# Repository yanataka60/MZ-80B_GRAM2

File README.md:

# MZ-80B GRAM2ボード

　MZ-80B OWNER'S MANUAL p67「図4-21 グラフィックメモリ2 MZ-8BK(オプション)」回路図から基板を起こしました。

　本体への装着方法は純正品と同じです。

## 回路図
　KiCadフォルダ内のMZ-80B_GRAM2.pdf参照

[回路図](https://github.com/yanataka60/MZ-80B_GRAM2/blob/main/Kicad/MZ-80B_GRAM2.pdf)

## 部品表
|番号|品名|数量|備考|
| ------------ | ------------ | ------------ | ------------ |
|C1|電解コンデンサ 16V100uF|1||
|C2-C12, C14, C16-C18|積層セラミックコンデンサ 0.1uF|15||
|C13|コンデンサ 470pF|1||
|C15|コンデンサ 220pF|1||
|J2,J3,J4,J5|使用しません|||
|J6|2x5ピンヘッダ|1|秋月電子通商 PH-2x40SG等|
|R1,R2|カーボン抵抗 1k|2||
|R3|カーボン抵抗 47Ω|1||
|R4|カーボン抵抗 100Ω|1||
|U1-U3,U9|74LS157|4|若松通商等|
|U4|74LS245|1|若松通商等|
|U5,U6,U10|74LS93|3|若松通商等|
|U7|74LS165|1|若松通商等|
|U11|74LS107|1|若松通商等|
|U13|74LS00|1|若松通商等|
|U14|74LS04|1|若松通商等|
|U15,U18|74LS32|2|若松通商等|
|U19|8kx8 SRAM 6264|1|若松通商等|
||2x5フラットケーブル|1|4番スロットなら20cm程度、1番スロットなら30cm程度|

## ボードの完成写真

## 取付方法
拡張I/Oユニットの1番スロット又は4番スロットにGRAM2ボードを挿し込みます。

GRAM1ボードのJ3とGRAM2ボードのJ6を2x5Pinケーブルで接続します。

## 追記
2025.10.10 回路図のpdfファイルを追加した。

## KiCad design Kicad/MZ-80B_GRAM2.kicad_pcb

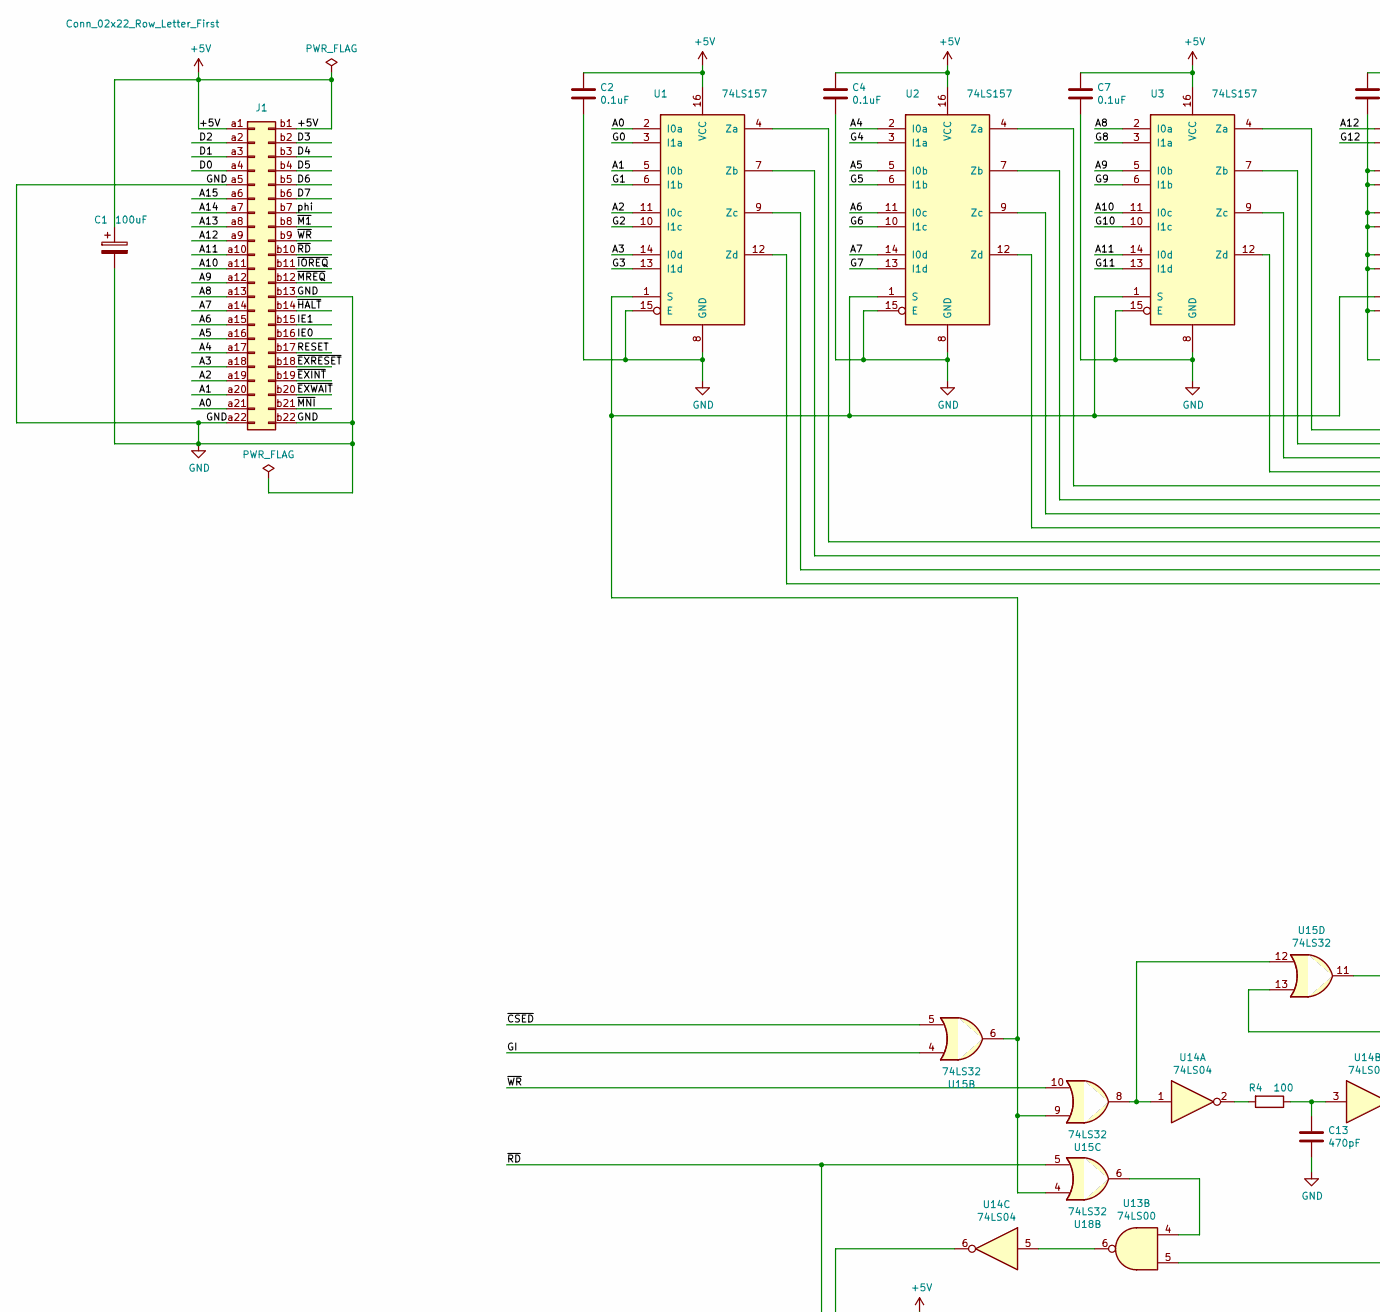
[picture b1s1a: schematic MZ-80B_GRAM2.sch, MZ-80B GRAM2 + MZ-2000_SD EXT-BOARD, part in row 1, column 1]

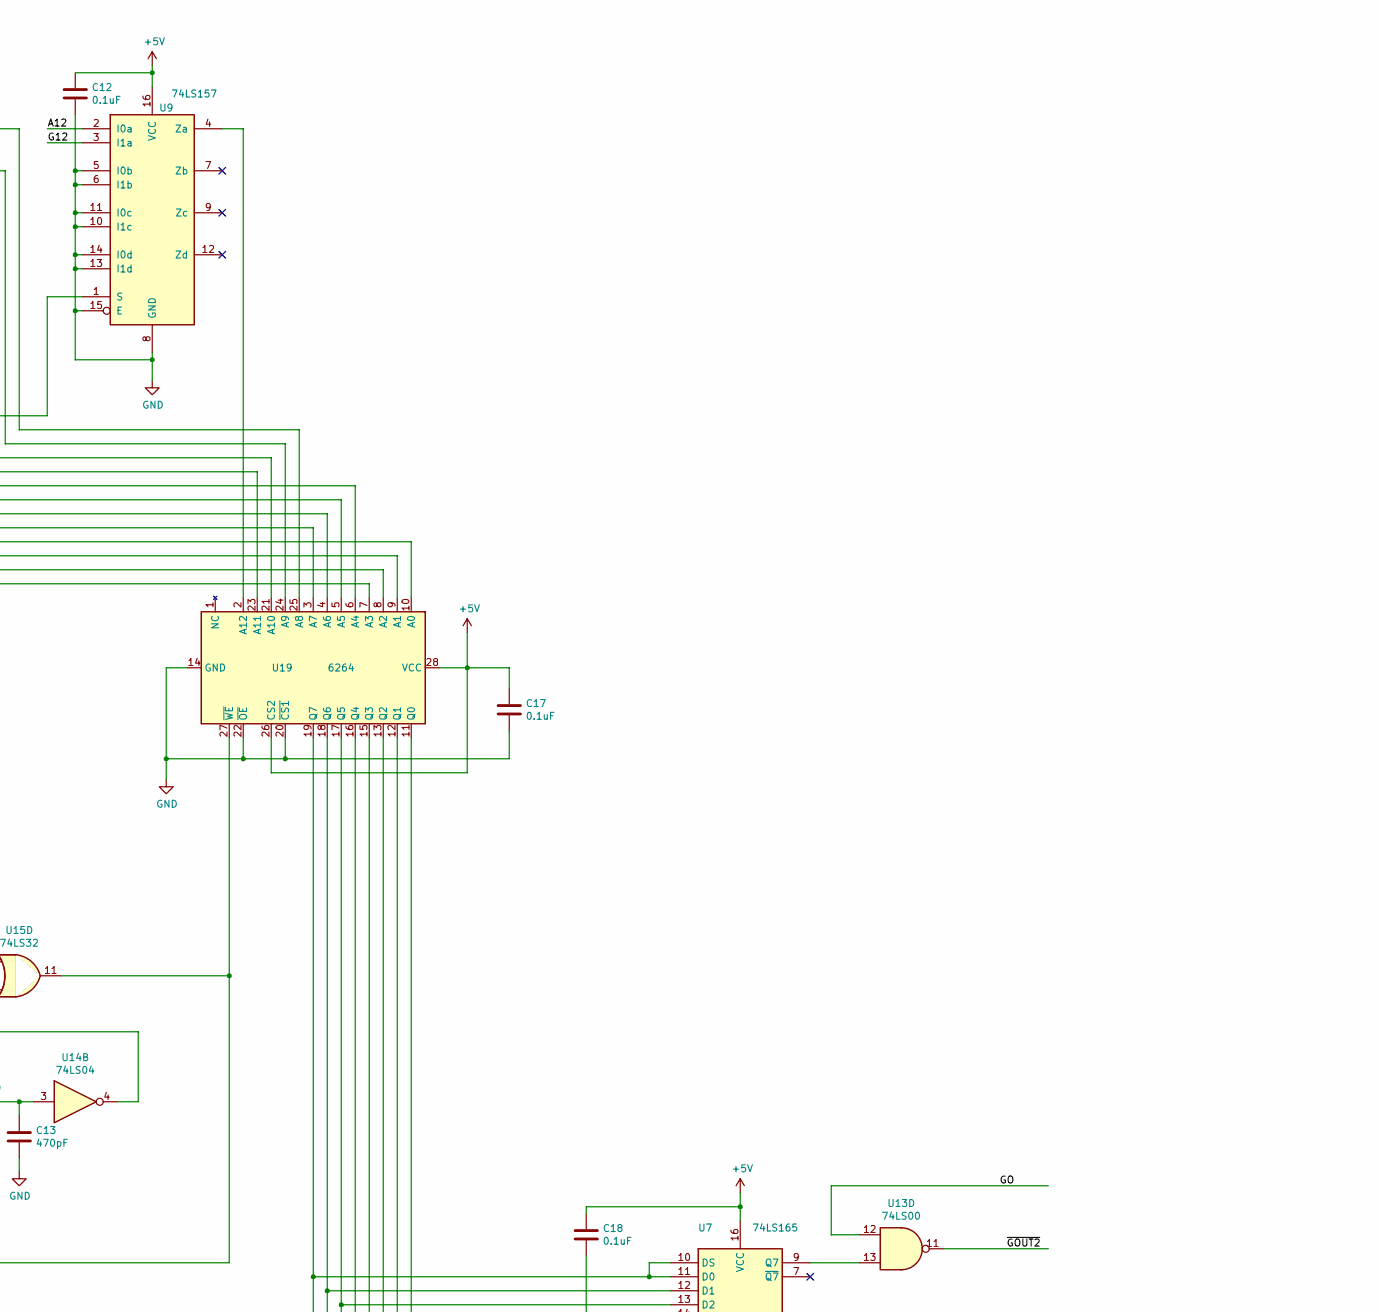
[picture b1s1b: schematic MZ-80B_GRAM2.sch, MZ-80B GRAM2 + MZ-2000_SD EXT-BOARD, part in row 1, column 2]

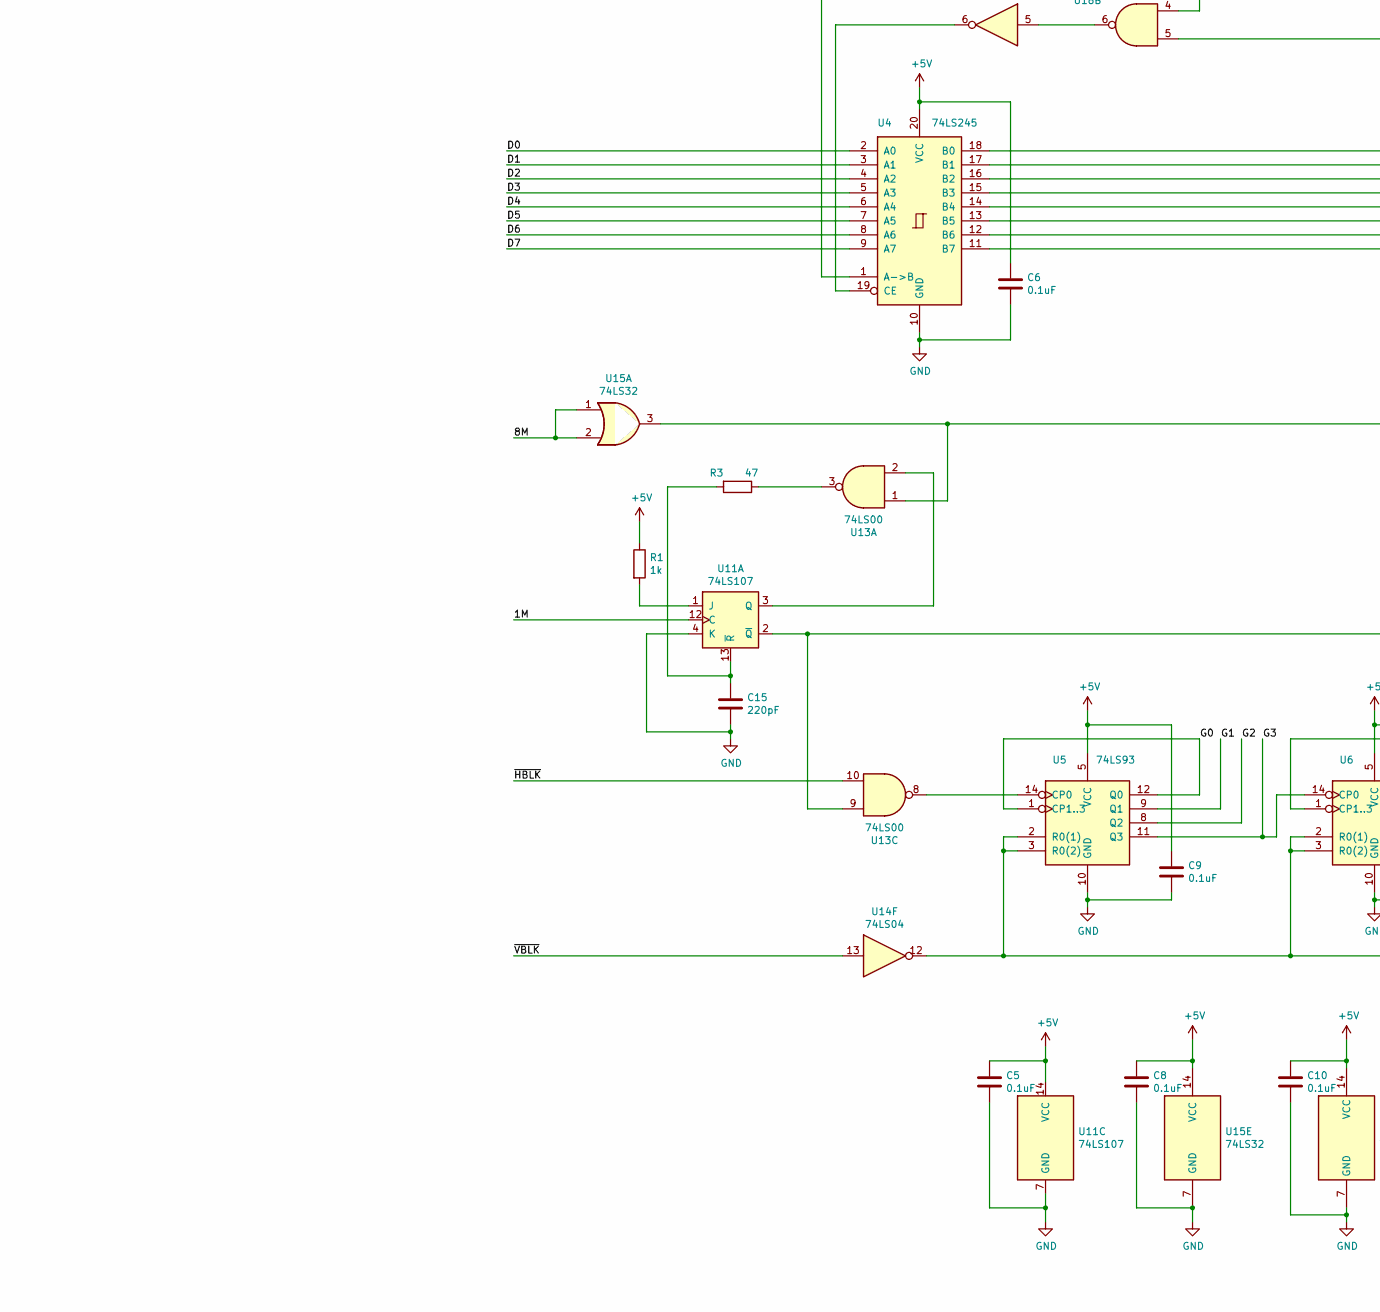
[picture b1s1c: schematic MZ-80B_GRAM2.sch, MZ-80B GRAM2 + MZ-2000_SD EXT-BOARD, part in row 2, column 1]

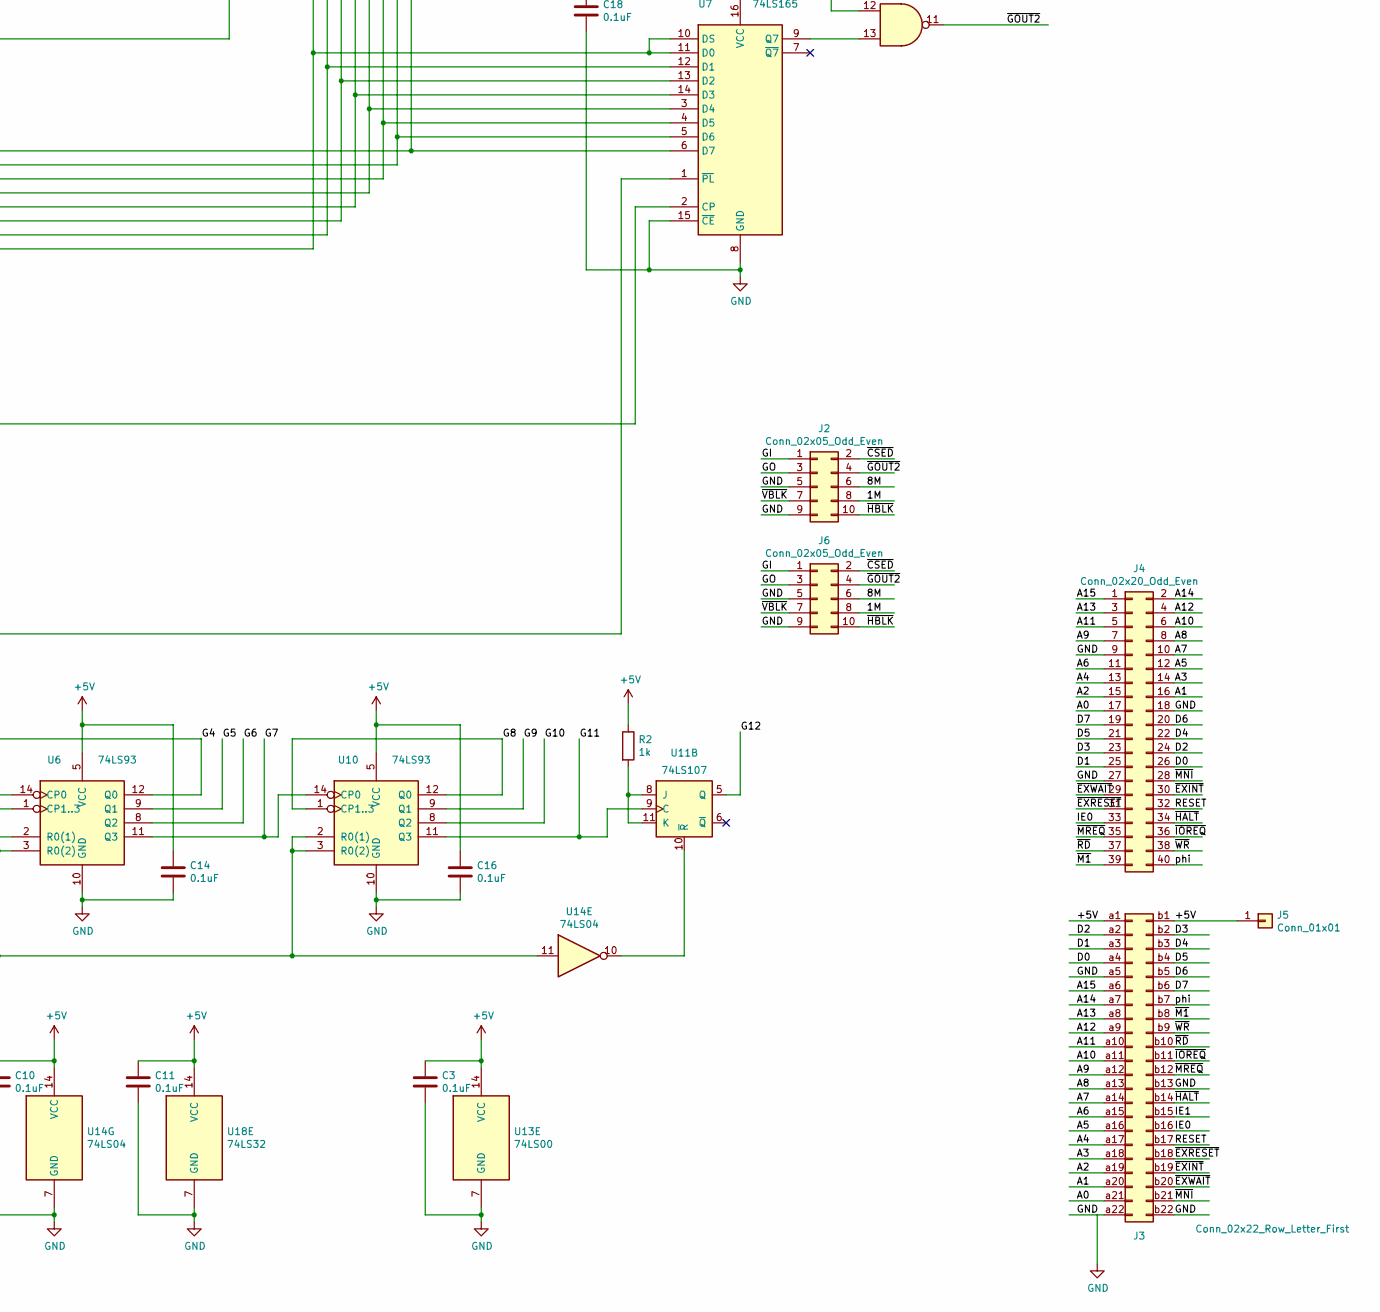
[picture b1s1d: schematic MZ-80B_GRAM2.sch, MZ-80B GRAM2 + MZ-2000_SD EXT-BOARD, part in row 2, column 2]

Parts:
C1: 100uF; CP_Radial_D5.0mm_P2.50mm
C2, C3, C4, C5, C6, C7, C8, C9, C10, C11, C12, C14, C16, C17, C18: 0.1uF; C_Rect_L4.0mm_W2.5mm_P2.50mm
C13: 470pF; C_Rect_L4.0mm_W2.5mm_P2.50mm
C15: 220pF; C_Rect_L4.0mm_W2.5mm_P2.50mm
J1: Conn_02x22_Row_Letter_First; BUS_MZ2000
J2, J6: Conn_02x05_Odd_Even; PinHeader_2x05_P2.54mm_Vertical
J3: Conn_02x22_Row_Letter_First; PinHeader_2x22_P2.54mm_Vertical
J4: Conn_02x20_Odd_Even; PinHeader_2x20_P2.54mm_Vertical
J5: Conn_01x01; PinHeader_1x01_P2.54mm_Vertical
R1, R2: 1k; R_Axial_DIN0207_L6.3mm_D2.5mm_P7.62mm_Horizontal
R3: 47; R_Axial_DIN0207_L6.3mm_D2.5mm_P7.62mm_Horizontal
R4: 100; R_Axial_DIN0207_L6.3mm_D2.5mm_P7.62mm_Horizontal
U1, U2, U3, U9: 74LS157; DIP-16_W7.62mm_LongPads
U4: 74LS245; DIP-20_W7.62mm_LongPads
U5, U6, U10: 74LS93; DIP-14_W7.62mm_LongPads
U7: 74LS165; DIP-16_W7.62mm_LongPads
U11: 74LS107; DIP-14_W7.62mm_LongPads
U13: 74LS00; DIP-14_W7.62mm_LongPads
U14: 74LS04; DIP-14_W7.62mm_LongPads
U15, U18: 74LS32; DIP-14_W7.62mm_LongPads
U19: 6264; DIP-28_W15.24mm_LongPads

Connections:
+5V: C1.1, C2.1, C3.1, C4.1, C5.1, C6.1, C7.1, C8.1, C9.1, C10.1, C11.1, C12.1, C14.1, C16.1, C17.1, C18.1, J1.a1, J1.b1, J3.a1, J3.b1, J5.1, R1.1, R2.1, U1.16 (VCC), U2.16 (VCC), U3.16 (VCC), U4.20 (VCC), U5.5 (VCC), U6.5 (VCC), U7.16 (VCC), U9.16 (VCC), U10.5 (VCC), U11.14 (VCC), U13.14 (VCC), U14.14 (VCC), U15.14 (VCC), U18.14 (VCC), U19.26 (CS2), U19.28 (VCC)
/1M: J2.8, J6.8, U11.12 (C)
/8M: J2.6, J6.6, U15.1, U15.2
/A0: J1.a21, J3.a21, J4.17, U1.2 (I0a)
/A1: J1.a20, J3.a20, J4.16, U1.5 (I0b)
/A2: J1.a19, J3.a19, J4.15, U1.11 (I0c)
/A3: J1.a18, J3.a18, J4.14, U1.14 (I0d)
/A4: J1.a17, J3.a17, J4.13, U2.2 (I0a)
/A5: J1.a16, J3.a16, J4.12, U2.5 (I0b)
/A6: J1.a15, J3.a15, J4.11, U2.11 (I0c)
/A7: J1.a14, J3.a14, J4.10, U2.14 (I0d)
/A8: J1.a13, J3.a13, J4.8, U3.2 (I0a)
/A9: J1.a12, J3.a12, J4.7, U3.5 (I0b)
/A10: J1.a11, J3.a11, J4.6, U3.11 (I0c)
/A11: J1.a10, J3.a10, J4.5, U3.14 (I0d)
/A12: J1.a9, J3.a9, J4.4, U9.2 (I0a)
/A13: J1.a8, J3.a8, J4.3
/A14: J1.a7, J3.a7, J4.2
/A15: J1.a6, J3.a6, J4.1
/D0: J1.a4, J3.a4, J4.26, U4.2 (A0)
/D1: J1.a3, J3.a3, J4.25, U4.3 (A1)
/D2: J1.a2, J3.a2, J4.24, U4.4 (A2)
/D3: J1.b2, J3.b2, J4.23, U4.5 (A3)
/D4: J1.b3, J3.b3, J4.22, U4.6 (A4)
/D5: J1.b4, J3.b4, J4.21, U4.7 (A5)
/D6: J1.b5, J3.b5, J4.20, U4.8 (A6)
/D7: J1.b6, J3.b6, J4.19, U4.9 (A7)
/G0: U1.3 (I1a), U5.1 (CP1..3), U5.12 (Q0)
/G1: U1.6 (I1b), U5.9 (Q1)
/G2: U1.10 (I1c), U5.8 (Q2)
/G3: U1.13 (I1d), U5.11 (Q3), U6.14 (CP0)
/G4: U2.3 (I1a), U6.1 (CP1..3), U6.12 (Q0)
/G5: U2.6 (I1b), U6.9 (Q1)
/G6: U2.10 (I1c), U6.8 (Q2)
/G7: U2.13 (I1d), U6.11 (Q3), U10.14 (CP0)
/G8: U3.3 (I1a), U10.1 (CP1..3), U10.12 (Q0)
/G9: U3.6 (I1b), U10.9 (Q1)
/G10: U3.10 (I1c), U10.8 (Q2)
/G11: U3.13 (I1d), U10.11 (Q3), U11.9 (C)
/G12: U9.3 (I1a), U11.5 (Q)
/GI: J2.1, J6.1, U15.4
/GO: J2.3, J6.3, U13.12
/IE0: J1.b16, J3.b16, J4.33
/IE1: J1.b15, J3.b15
/RESET: J1.b17, J3.b17, J4.32
/phi: J1.b7, J3.b7, J4.40
/~CSED: J2.2, J6.2, U15.5
/~EXINT: J1.b19, J3.b19, J4.30
/~EXRESET: J1.b18, J3.b18, J4.31
/~EXWAIT: J1.b20, J3.b20, J4.29
/~GOUT2: J2.4, J6.4, U13.11
/~HALT: J1.b14, J3.b14, J4.34
/~HBLK: J2.10, J6.10, U13.10
/~IOREQ: J1.b11, J3.b11, J4.36
/~M1: J1.b8, J3.b8, J4.39
/~MNI: J1.b21, J3.b21, J4.28
/~MREQ: J1.b12, J3.b12, J4.35
/~RD: J1.b10, J3.b10, J4.37, U4.1 (A->B), U18.5
/~VBLK: J2.7, J6.7, U14.13
/~WR: J1.b9, J3.b9, J4.38, U15.10
GND: C1.2, C2.2, C3.2, C4.2, C5.2, C6.2, C7.2, C8.2, C9.2, C10.2, C11.2, C12.2, C13.2, C14.2, C15.2, C16.2, C17.2, C18.2, J1.a5, J1.a22, J1.b13, J1.b22, J2.5, J2.9, J3.a5, J3.a22, J3.b13, J3.b22, J4.9, J4.18, J4.27, J6.5, J6.9, U1.8 (GND), U1.15 (E), U2.8 (GND), U2.15 (E), U3.8 (GND), U3.15 (E), U4.10 (GND), U5.10 (GND), U6.10 (GND), U7.8 (GND), U7.15 (~CE), U9.5 (I0b), U9.6 (I1b), U9.8 (GND), U9.10 (I1c), U9.11 (I0c), U9.13 (I1d), U9.14 (I0d), U9.15 (E), U10.10 (GND), U11.4 (K), U11.7 (GND), U13.7 (GND), U14.7 (GND), U15.7 (GND), U18.7 (GND), U19.14 (GND), U19.20 (~CS1), U19.22 (~OE)
unnamed: C13.1, R4.1, U14.3
unnamed: C15.1, R3.2, U11.13 (~R)
unnamed: R1.2, U11.1 (J)
unnamed: R2.2, U11.8 (J), U11.11 (K)
unnamed: R3.1, U13.3
unnamed: R4.2, U14.2
unnamed: U1.1 (S), U2.1 (S), U3.1 (S), U9.1 (S), U15.6, U15.9, U18.4
unnamed: U1.4 (Za), U19.10 (A0)
unnamed: U1.7 (Zb), U19.9 (A1)
unnamed: U1.9 (Zc), U19.8 (A2)
unnamed: U1.12 (Zd), U19.7 (A3)
unnamed: U5.2 (R0(1)), U5.3 (R0(2)), U6.2 (R0(1)), U6.3 (R0(2)), U10.2 (R0(1)), U10.3 (R0(2)), U14.11, U14.12
unnamed: U7.1 (~PL), U11.2 (~Q), U13.9
unnamed: U11.3 (Q), U13.2
unnamed: U11.10 (~R), U14.10
unnamed: U7.2 (CP), U13.1, U15.3
unnamed: U13.4, U18.6
unnamed: U13.5, U15.11, U19.27 (~WE)
unnamed: U13.6, U14.5
unnamed: U5.14 (CP0), U13.8
unnamed: U7.9 (Q7), U13.13
unnamed: U14.1, U15.8, U15.12
unnamed: U14.4, U15.13
unnamed: U4.19 (CE), U14.6
unnamed: U9.4 (Za), U19.2 (A12)
unnamed: U2.12 (Zd), U19.3 (A7)
unnamed: U2.9 (Zc), U19.4 (A6)
unnamed: U2.7 (Zb), U19.5 (A5)
unnamed: U2.4 (Za), U19.6 (A4)
unnamed: U4.18 (B0), U7.6 (D7), U19.11 (Q0)
unnamed: U4.17 (B1), U7.5 (D6), U19.12 (Q1)
unnamed: U4.16 (B2), U7.4 (D5), U19.13 (Q2)
unnamed: U4.15 (B3), U7.3 (D4), U19.15 (Q3)
unnamed: U4.14 (B4), U7.14 (D3), U19.16 (Q4)
unnamed: U4.13 (B5), U7.13 (D2), U19.17 (Q5)
unnamed: U4.12 (B6), U7.12 (D1), U19.18 (Q6)
unnamed: U4.11 (B7), U7.10 (DS), U7.11 (D0), U19.19 (Q7)
unnamed: U3.9 (Zc), U19.21 (A10)
unnamed: U3.12 (Zd), U19.23 (A11)
unnamed: U3.7 (Zb), U19.24 (A9)
unnamed: U3.4 (Za), U19.25 (A8)

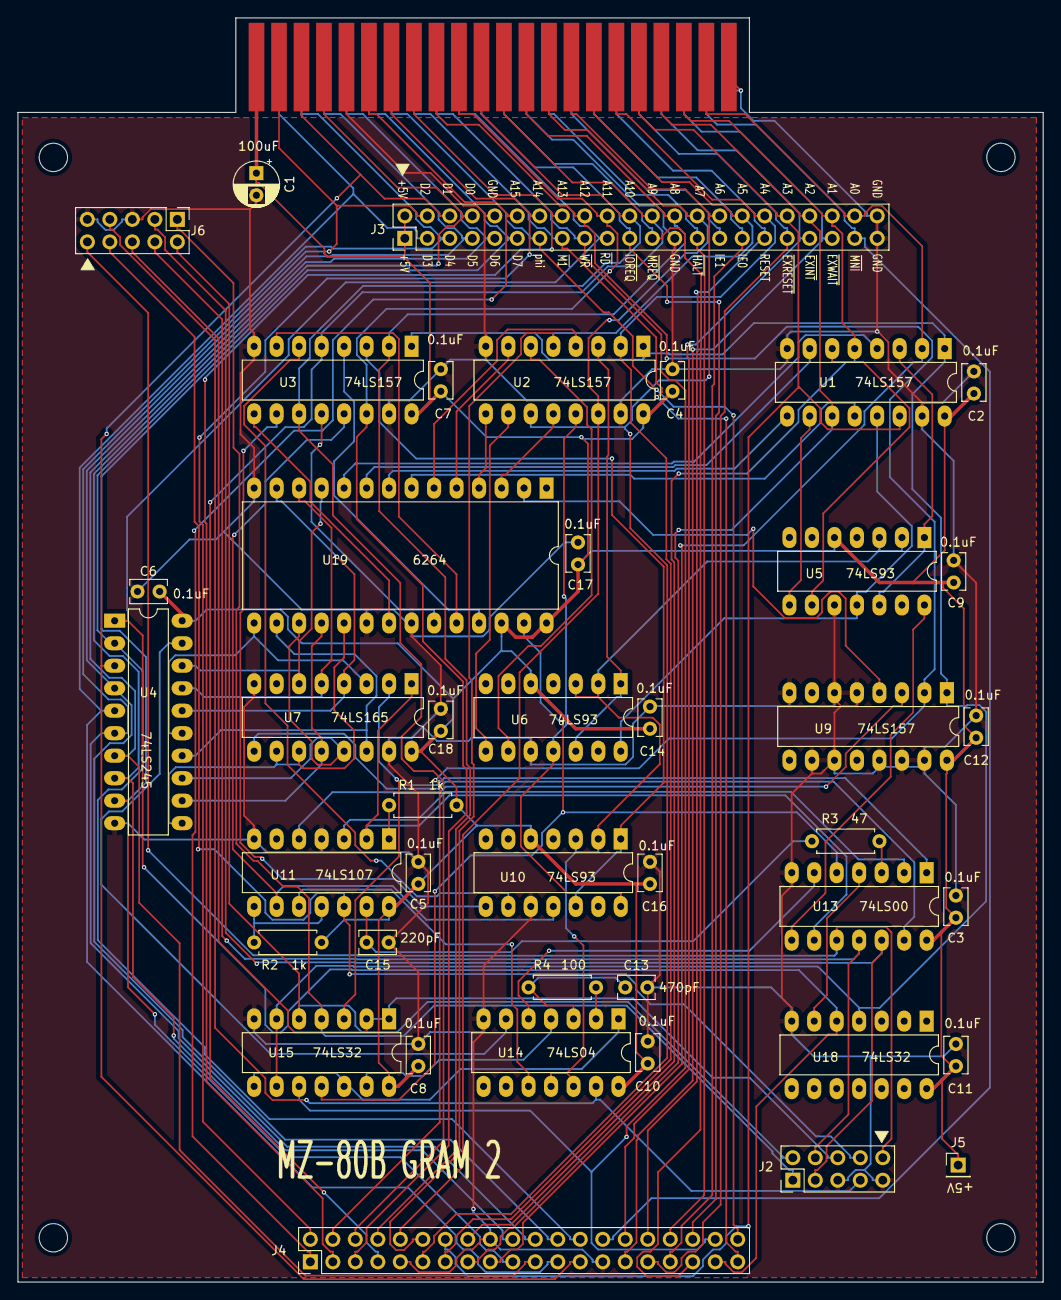
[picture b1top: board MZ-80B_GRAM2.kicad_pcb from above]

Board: 2 copper layers, 115.8 x 142.7 mm, 47 parts (0 on the bottom side), 102 nets.

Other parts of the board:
MH1, MH2, MH3, MH4: MountingHole_3.2mm_M3
